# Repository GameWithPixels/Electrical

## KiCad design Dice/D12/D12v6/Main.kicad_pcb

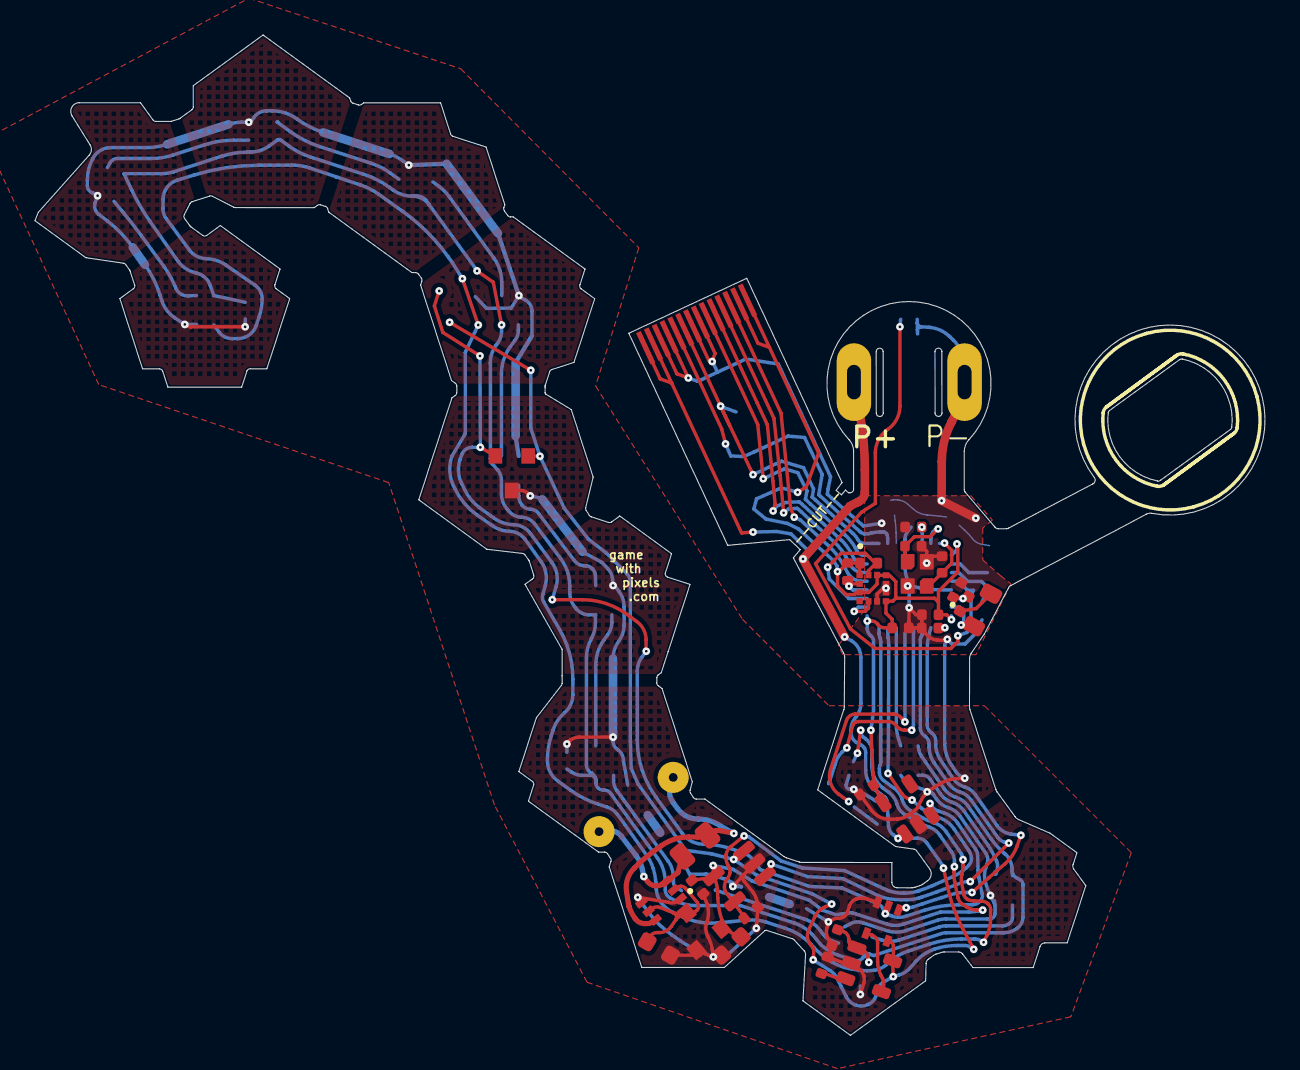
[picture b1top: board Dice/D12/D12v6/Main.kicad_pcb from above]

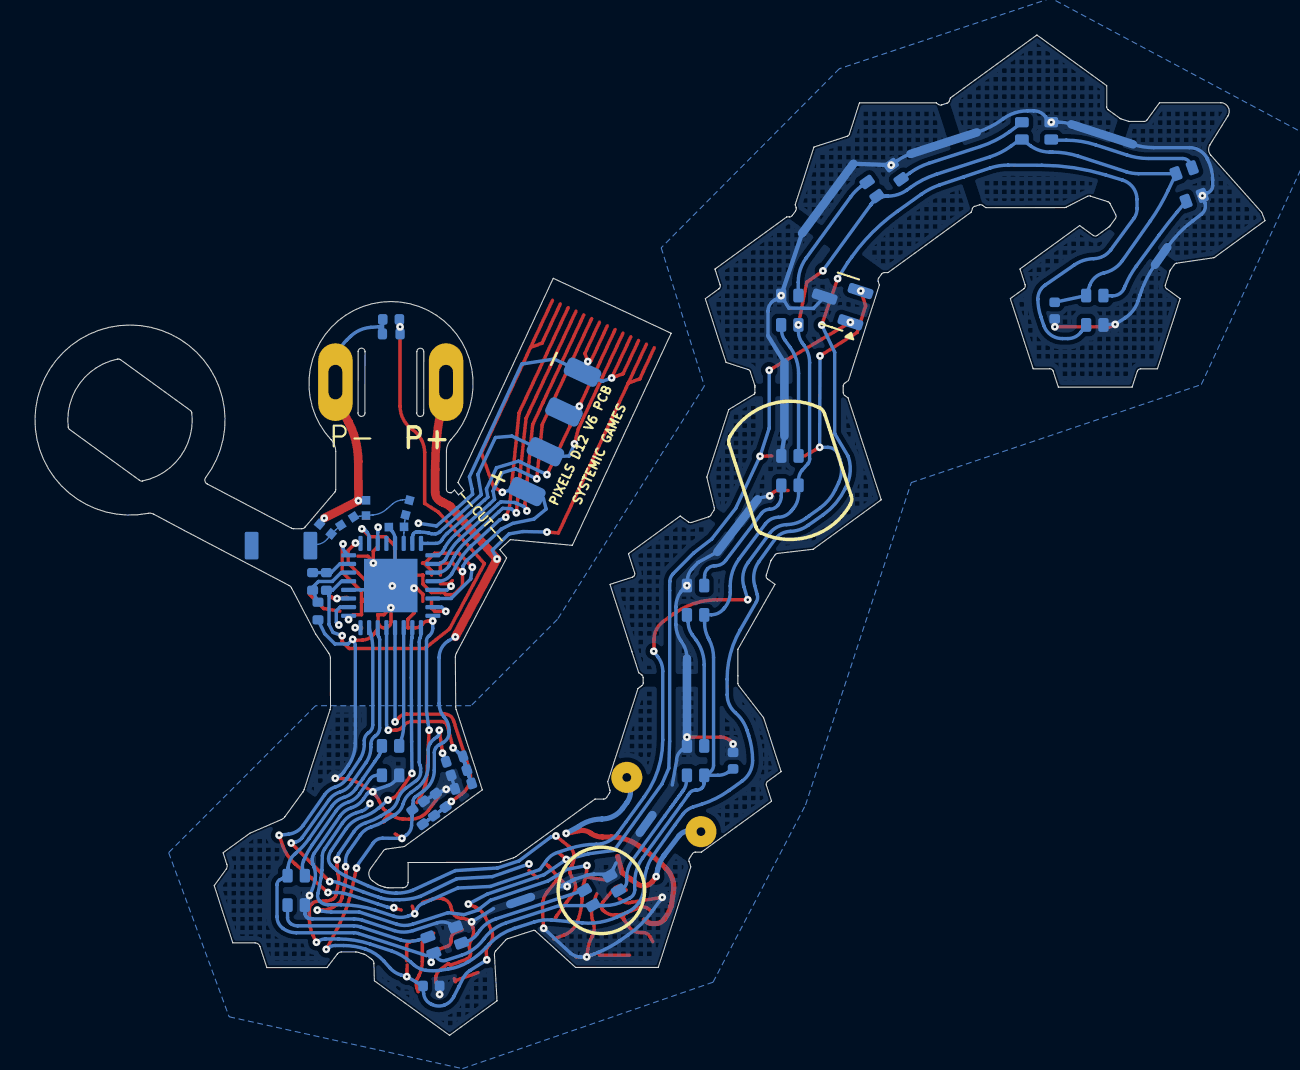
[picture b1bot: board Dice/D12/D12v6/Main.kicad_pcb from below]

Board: 2 copper layers, 71.2 x 57.9 mm, 67 parts (38 on the bottom side), 51 nets.

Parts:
AE1: Antenna_Chip; CHIP_ANT
C1, C4, C18: 4.7uF 10V 20%; C_0402_1005Metric
C2, C5: 8pF 10V 10%; C_0402_1005Metric
C3, C10, C23, C24: 0.1uF 10V 20%; C_0402_1005Metric
C6: DNP; C_0402_1005Metric
C7: 100pF NP0 10V 5%; C_0402_1005Metric
C8: 0.8pF 10V 5% C0G; 0402_RF
C9, C16: 10uF 10V 20%; C_0402_1005Metric
C11, C12: DNP; 0402_RF
C13: 4.7uF 25V 20%; C_0603_1608Metric
C15: 22uF 10V 20%; C_0603_1608Metric
C19: 12nF 50V 5% NP0; C_0805_2012Metric
C21, C22: 10nF 25V 10%; C_0402_1005Metric
D1: BAV99S; SOT-363_SC-70-6
D2, D3, D4, D5, D6, D7, D8, D9, D10, D11, D12, D13: TX1812Z_2020
J1: Conn_01x14; FPC_14
J2: Conn_01x04; FPC-POGO-4
J3: Conn_01x02; Hongjie 10100 Connector
L1: 10uH 100mA 20%; L_0805_2012Metric
L2: 15nH 100mA 5%; L_0402_1005Metric
L3: 0 Ohm; 0402_RF
L5: 3.9nH 5%; 0402_RF
P5: COILA; TestPoint_THTPad_D1.5mm_Drill0.7mm_nosilk
P6: COILB; TestPoint_THTPad_D1.5mm_Drill0.7mm_nosilk
R1, R2, R7: 4.02M 1%; R_0402_1005Metric
R3: 10k 5%; R_0402_1005Metric
R4, R6: 18k 1%; R_0402_1005Metric
R5, R10: 100k 1%; R_0402_1005Metric
R8: 10M 1%; R_0402_1005Metric
R9: 180k 1%; R_0402_1005Metric
R12, R16: 2.7k 5%; R_0402_1005Metric
TH1: NTC 100k @ 25C; R_0402_1005Metric
U1: N52810_QFN32; QFN-32-1EP_5x5mm_P0.5mm_EP3.1x3.1mm
U2: KXTJ3-1057; LGA-12_2x2mm_P0.5mm
U3: PJ75BL50SA; SOT-23
U4: ME6215; SOT-23-5
U5: MCP73832T-2ACI/OT; SOT-23-5
U6: MT9700; SOT-23-5
U7: SN74LVC1G08; SOT-353_SC-70-5
U8, U8-alt1: VCS2373S; SOT-23
Y1: 32MHz 40ppm; Crystal_SMD_2016-4Pin_2.0x1.6mm

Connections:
+5V: C15.1, R1.1, R4.1, U3.2 (VOUT), U5.4 (VDD)
+BATT: C16.1, J1.1, J1.2, J3.1, R7.1, U4.1 (VIN), U5.3 (VBAT), U6.5 (VIN), U7.5 (VCC), U8.1 (VCC), U8-alt1.1 (VCC)
/5V_SENSE: C21.1, R1.2, R2.2, U1.4 (P0.04/AIN2)
/ACC_INT: U1.10 (P0.12), U2.5 (INT)
/ANTENNA: AE1.1 (FEED), C11.1, L3.2
/ANT_50: C12.1, L3.1, L5.2
/ANT_NRF: C8.1, L5.1, U1.19 (ANT)
/BATT_NTC: C6.1, R5.2, TH1.1, U1.28 (P0.30/AIN6)
/LED_DATA: D2.1 (DIN), U1.6 (P0.06)
/LED_EN: U1.2 (P0.00/XL1), U7.1
/LED_RETURN: D13.3 (DOUT), U1.8 (P0.10)
/NTC_ID_VDD: R5.1, R10.2, U1.26 (P0.25)
/PROG: R6.1, U1.7 (P0.09), U5.5 (PROG)
/Power Supply/LED_EN_OUT: U6.4 (EN), U7.4
/Power Supply/MAG1_: U4.3 (CE), U7.2, U8.2 (OUT), U8-alt1.2 (OUT)
/SCL: R12.2, U1.11 (P0.14), U2.12 (SCL)
/SDA: R16.2, U1.12 (P0.15), U2.2 (SDA)
/STATS: U1.3 (P0.01/XL2), U5.1 (STAT)
/VBAT_SENSE: C22.1, R7.2, R8.1, U1.5 (P0.05/AIN3)
GND: C1.2, C2.1, C3.2, C4.2, C5.1, C6.2, C7.2, C8.2, C9.2, C10.2, C11.2, C12.2, C13.2, C15.2, C16.2, C18.2, C21.2, C22.2, C23.2, C24.2, D1.1 (A1), D1.4 (A3), D2.4 (GND), D3.4 (GND), D4.4 (GND), D5.4 (GND), D6.4 (GND), D7.4 (GND), D8.4 (GND), D9.4 (GND), D10.4 (GND), D11.4 (GND), D12.4 (GND), D13.4 (GND), J1.3, J1.4, J1.7, J1.8, J2.4, J3.2, R2.1, R3.2, R4.2, R6.2, R8.2, R9.1, TH1.2, U1.20 (VSS), U1.29 (VSS), U1.33 (VSS), U2.6 (GND), U2.8 (GND), U2.9 (GND), U3.1 (VSS), U4.2 (VSS), U5.2 (VSS), U6.2 (GND), U7.3 (GND), U8.3 (GND), U8-alt1.3 (GND), Y1.2, Y1.4
unnamed: C19.2, D1.6 (K3A4), P6.1
unnamed: C19.1, D1.3 (K1A2), P5.1
unnamed: D2.3 (DOUT), D3.1 (DIN)
unnamed: D3.3 (DOUT), D4.1 (DIN)
unnamed: D4.3 (DOUT), D5.1 (DIN)
unnamed: D5.3 (DOUT), D6.1 (DIN)
unnamed: D6.3 (DOUT), D7.1 (DIN)
unnamed: D7.3 (DOUT), D8.1 (DIN)
unnamed: D8.3 (DOUT), D9.1 (DIN)
unnamed: D9.3 (DOUT), D10.1 (DIN)
unnamed: D10.3 (DOUT), D11.1 (DIN)
unnamed: D11.3 (DOUT), D12.1 (DIN)
unnamed: D12.3 (DOUT), D13.1 (DIN)
unnamed: L1.2, L2.1
unnamed: L1.1, U1.31 (DCC)
unnamed: C3.1, U1.1 (DEC1)
unnamed: C7.1, U1.22 (DEC3)
unnamed: C1.1, L2.2, U1.30 (DEC4)
unnamed: R9.2, R10.1, U1.27 (P0.28/AIN4)
unnamed: C5.2, U1.23 (XC1), Y1.3
unnamed: C2.2, U1.24 (XC2), Y1.1
unnamed: R3.1, U6.3 (SET)
RESET: J1.9, U1.16 (P0.16)
RXI: J1.10, U1.15 (P0.20/TCLK)
SWDCLK: J1.6, J2.3, U1.17 (SWDCLK)
SWDIO: J1.5, J2.2, U1.18 (SWDIO)
SWO: J1.11, U1.14 (P0.18/TDATA0)
TXO: J1.12, U1.13 (P0.16/TDATA1)
VDC: C9.1, C23.1, C24.1, D2.2 (VCC), D3.2 (VCC), D4.2 (VCC), D5.2 (VCC), D6.2 (VCC), D7.2 (VCC), D8.2 (VCC), D9.2 (VCC), D10.2 (VCC), D11.2 (VCC), D12.2 (VCC), D13.2 (VCC), U6.1 (VOUT)
VDD: C4.1, C10.1, C18.1, J1.13, J1.14, J2.1, R12.1, R16.1, U1.9 (VDD), U1.25 (VDD), U1.32 (VDD), U2.1 (ADDR), U2.3 (IO_VDD), U2.7 (VDD), U2.10 (VDD), U2.11 (IO_VDD), U4.5 (VOUT)
VEE: C13.1, D1.2 (K2), D1.5 (K4), U3.3 (VIN)

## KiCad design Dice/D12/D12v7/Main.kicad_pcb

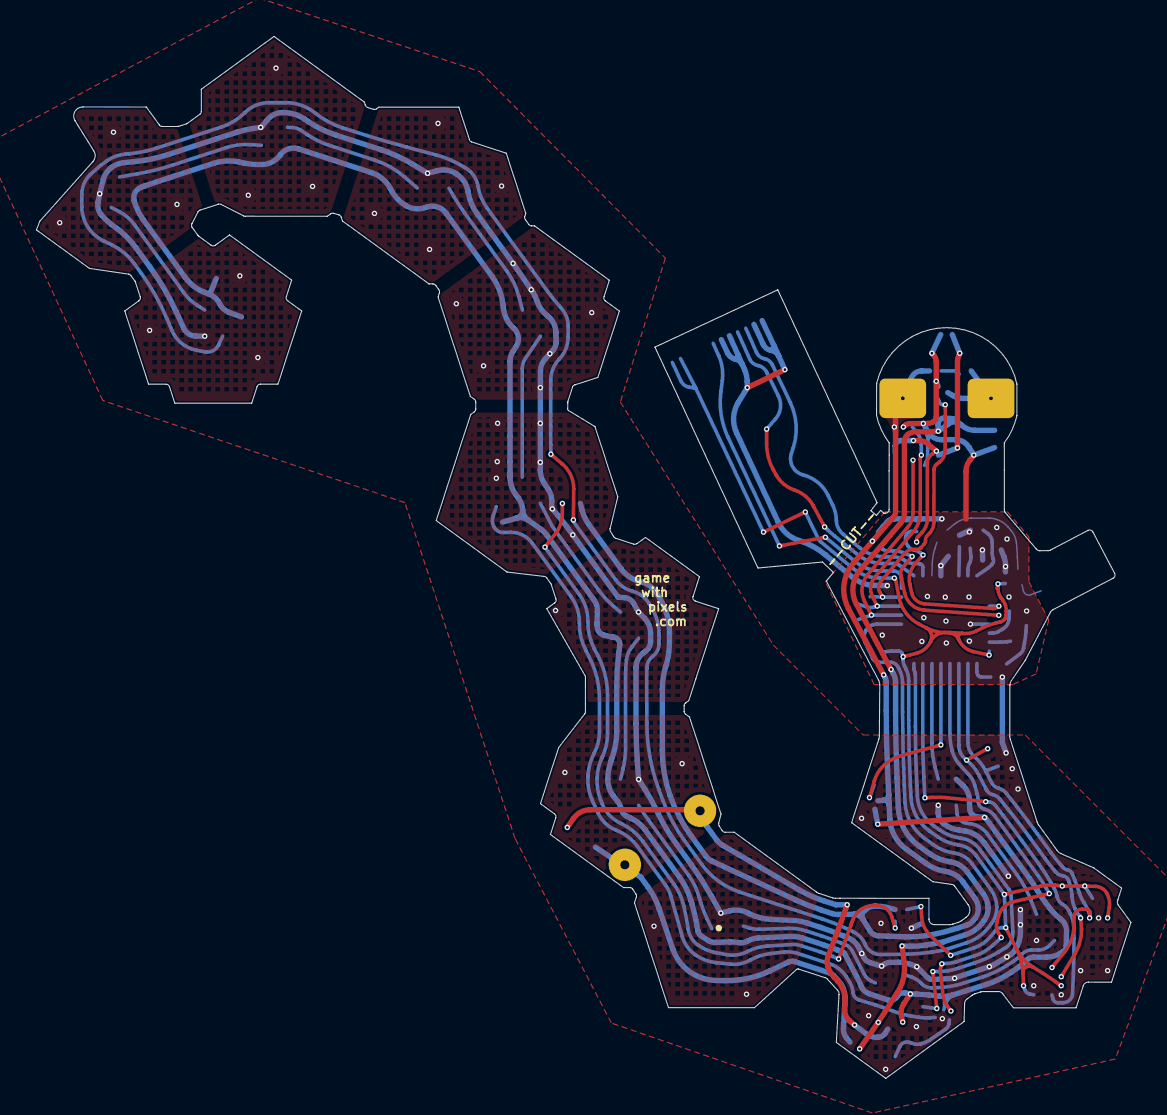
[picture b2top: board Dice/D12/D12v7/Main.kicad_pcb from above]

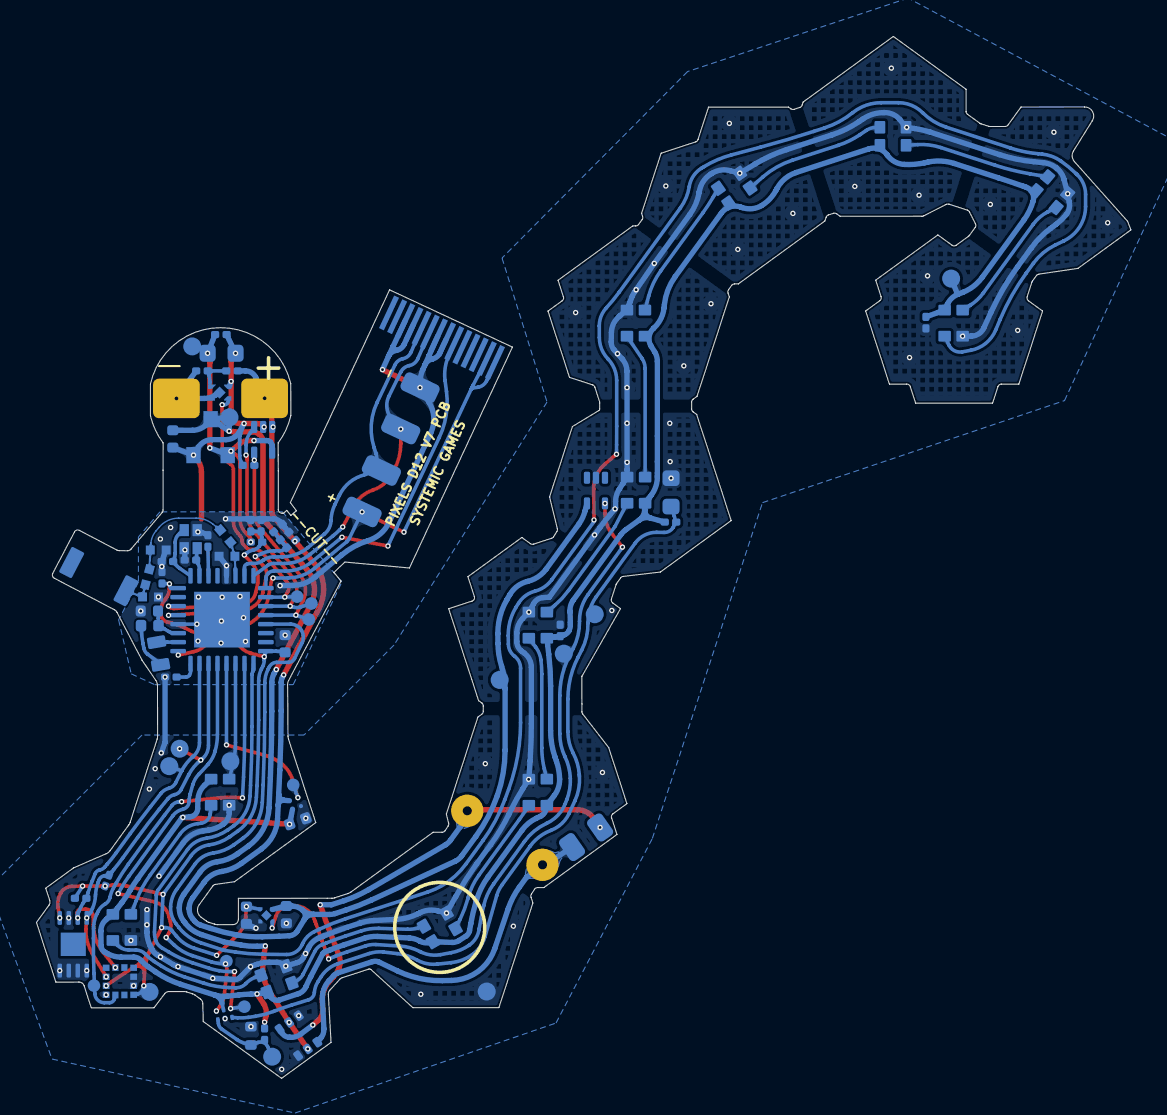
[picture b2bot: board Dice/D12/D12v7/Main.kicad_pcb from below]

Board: 2 copper layers, 60.8 x 57.9 mm, 87 parts (87 on the bottom side), 50 nets.

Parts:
AE1: Antenna_Chip; CHIP_ANT
C1, C4, C18: 4.7uF 10V 20%; C_0402_1005Metric
C2, C5: 8pF 10V 10%; C_0201_0603Metric
C3, C6, C10, C23, C24: 0.1uF 10V 20%; C_0201_0603Metric
C7: 100pF NP0 10V 2%; C_0201_0603Metric
C8: 0.8pF 10V 5% C0G; 0402_RF
C9, C16: 10uF 6.3V 20%; C_0402_1005Metric
C11, C12: DNP; 0402_RF
C13: 4.7uF 25V 20%; C_0402_1005Metric
C15: 22uF 10V 20%; C_0603_1608Metric
C19: 12nF 50V 5% NP0; C_0805_2012Metric
C21, C22: 10nF 25V 10%; C_0201_0603Metric
D1: BAV99S; SOT-363_SC-70-6
D2, D3, D4, D5, D6, D7, D8, D9, D10, D11, D12, D13: TX1812MWCA5-F01
J1: Conn_01x14; FPC_14
J2: Conn_01x04; FPC-POGO-4
J3: Conn_01x02; Hongjie 10100 Solder Tabs
L1: 10uH 100mA 20%; C_1.2x1.8
L2: 15nH 100mA 5%; L_0402_1005Metric
L3: 0 Ohm; 0402_RF
L5: 3.9nH 5%; 0402_RF
P5: COILA; TestPoint_THTPad_D1.5mm_Drill0.7mm_nosilk
P6: COILB; TestPoint_THTPad_D1.5mm_Drill0.7mm_nosilk
Q1: ZSPT-Z1608C-06F-Z4; D_0603_1608Metric
R1, R2, R7: 3.9M 1%; R_0201_0603Metric
R4, R5: 10k 1%; R_0201_0603Metric
R6, R10, R11: 3.9k 1%; R_0201_0603Metric
R8: 10M 1%; R_0201_0603Metric
R9: 100k 1%; R_0201_0603Metric
R12: 510R 1%; R_0201_0603Metric
TH1: NTC 100k @ 25C; R_0402_1005Metric
U1: N52810_QFN32; QFN-32-1EP_5x5mm_P0.5mm_EP3.1x3.1mm
U2: SC7A20HTR; LGA-12_2x2mm_P0.5mm
U3: PJ75BL50SA; SOT-23
U4: ME6230; FPB1_1-4
U5: BL24C02F-NTRC; TDFN-8-1EP_3x2mm_P0.5mm_EP1.3x1.4mm
U6: AW35122
U7: DS6101; UDFN-4-1EP_1x1mm_P0.65mm_EP0.48x0.48mm
U8: SL1605; SOT-553
U9: XT4051; SOT-553
U10: WAS3157D-6/TR; DFN1109-6
W1: LED_DATA1; TEST_PIN
W2: PROG; TEST_PIN
W3: PHOTO; TEST_PIN
W4: VDC; TEST_PIN
W5: SM; TEST_PIN
W6: MAG1; TEST_PIN
W7: ACC_INT; TEST_PIN
W8: SCL; TEST_PIN
W9: SDA; TEST_PIN
W14: BATT; TEST_PIN
W15: +5V; TEST_PIN
W16: VIN; TEST_PIN
W17: STAT; TEST_PIN
W19: GND; TEST_PIN
W20: TH1; TEST_PIN
W21: LED2; TEST_PIN
W22: ADC_SELECT; TEST_PIN
W23: ADC_OUT; TEST_PIN
W25: VDD; TEST_PIN
Y1: 32MHz 40ppm; SX16Y032000B81T001

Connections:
+5V: C15.1, R1.1, R4.1, U3.2 (VOUT), U9.5 (VCC), W15.1
+BATT: C16.1, J3.1, R7.1, R12.1, U4.4 (VIN), U6.A2 (VIN), U8.4 (VDD), U9.1 (BAT), W14.1
/5V_SENSE: C21.1, R1.2, R2.2, U1.27 (P0.28/AIN4)
/ACC_INT: U1.7 (P0.09), U2.5 (INT1), W7.1
/ANTENNA: AE1.1 (FEED), C11.1, L3.2
/ANT_50: C12.1, L3.1, L5.2
/ANT_NRF: C8.1, L5.1, U1.19 (ANT)
/LED_DATA: D2.3 (DIN), U1.6 (P0.06), W1.1
/LED_EN: U1.5 (P0.05/AIN3), U6.B2 (EN), W21.1
/LED_RETURN: D13.1 (DOUT), U1.12 (P0.15)
/MAG1_: U4.3 (CE), U8.5 (OUT), W6.1
/NTC_PHOTO_SENSE: U1.4 (P0.04/AIN2), U10.6 (A), W23.1
/OPT_A2D: Q1.1 (C), R5.2, U10.3 (B1), W3.1
/PROG: R6.1, U1.13 (P0.16/TDATA1), U9.4 (PROG), W2.1
/SCL: R10.2, U1.2 (P0.00/XL1), U2.12 (SCL), U5.6 (SCL), W8.1
/SDA: R11.2, U1.3 (P0.01/XL2), U2.2 (SDA), U5.5 (SDA), W9.1
/SENSE_SELECT: U1.8 (P0.10), U10.4 (S), W22.1
/SM: U1.15 (P0.20/TCLK), U7.3 (SM), W5.1
/STATS: U1.14 (P0.18/TDATA0), U9.3 (CHRG), W17.1
/VBAT_SENSE: C22.1, R7.2, R8.1, U1.28 (P0.30/AIN6)
/Wireless Charging/B-: C23.2, J3.2, U7.2 (VSS), U7.5 (PAD)
/Wireless Charging/COILA: C19.1, D1.3 (K1A2), P5.1
/Wireless Charging/COILB: C19.2, D1.6 (K3A4), P6.1
/Wireless Charging/TH1: R9.2, TH1.1, U10.1 (B0), W20.1
GND: C1.2, C2.1, C3.2, C4.2, C5.1, C6.2, C7.2, C8.2, C9.2, C10.2, C11.2, C12.2, C13.2, C15.2, C16.2, C18.2, C21.2, C22.2, C24.2, D1.1 (A1), D1.4 (A3), D2.2 (GND), D3.2 (GND), D4.2 (GND), D5.2 (GND), D6.2 (GND), D7.2 (GND), D8.2 (GND), D9.2 (GND), D10.2 (GND), D11.2 (GND), D12.2 (GND), D13.2 (GND), J1.3, J1.4, J1.7, J1.8, J2.4, Q1.2 (E), R2.1, R4.2, R6.2, R8.2, TH1.2, U1.20 (VSS), U1.29 (VSS), U1.33 (VSS), U2.4 (NC), U2.8 (GND), U2.9 (GND), U3.1 (VSS), U4.2 (VSS), U5.1 (A0), U5.2 (A1), U5.3 (A2), U5.4 (GND), U5.7 (WP), U6.B1 (GND), U7.4 (EB-), U8.2 (GND), U9.2 (GND), U10.2 (GND), W19.1, Y1.2, Y1.4
unnamed: D2.1 (DOUT), D3.3 (DIN)
unnamed: D3.1 (DOUT), D4.3 (DIN)
unnamed: D4.1 (DOUT), D5.3 (DIN)
unnamed: D5.1 (DOUT), D6.3 (DIN)
unnamed: D6.1 (DOUT), D7.3 (DIN)
unnamed: D7.1 (DOUT), D8.3 (DIN)
unnamed: D8.1 (DOUT), D9.3 (DIN)
unnamed: D9.1 (DOUT), D10.3 (DIN)
unnamed: D10.1 (DOUT), D11.3 (DIN)
unnamed: D11.1 (DOUT), D12.3 (DIN)
unnamed: D12.1 (DOUT), D13.3 (DIN)
unnamed: L1.2, L2.1
unnamed: L1.1, U1.31 (DCC)
unnamed: C3.1, U1.1 (DEC1)
unnamed: C7.1, U1.22 (DEC3)
unnamed: C1.1, L2.2, U1.30 (DEC4)
unnamed: C5.2, U1.23 (XC1), Y1.3
unnamed: C2.2, U1.24 (XC2), Y1.1
unnamed: C23.1, R12.2, U7.1 (BAT)
RESET: J1.9, U1.16 (P0.16)
SWDCLK: J1.6, J2.3, U1.17 (SWDCLK)
SWDIO: J1.5, J2.2, U1.18 (SWDIO)
VDC: C6.1, C9.1, C24.1, D2.4 (VCC), D3.4 (VCC), D4.4 (VCC), D5.4 (VCC), D6.4 (VCC), D7.4 (VCC), D8.4 (VCC), D9.4 (VCC), D10.4 (VCC), D11.4 (VCC), D12.4 (VCC), D13.4 (VCC), R5.1, R9.1, U6.A1 (VOUT), U10.5 (VCC), W4.1
VDD: C4.1, C10.1, C18.1, J1.13, J1.14, J2.1, R10.1, R11.1, U1.9 (VDD), U1.25 (VDD), U1.32 (VDD), U2.3 (IO_VDD), U2.7 (VDD), U4.1 (VOUT), U5.8 (VCC), W25.1
VEE: C13.1, D1.2 (K2), D1.5 (K4), U3.3 (VIN), W16.1

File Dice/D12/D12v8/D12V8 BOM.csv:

"Reference","Qty","Value","Footprint","Manufacturer","Part Number"
"AE1","1","Antenna_Chip","Pixels-dice:CHIP_ANT","Microgate","MGMA3216H2450-A02"
"C1,C4,C18","3","4.7uF 10V 20%","Pixels-dice:C_0402_1005Metric","HRE","CGA0402X5R475M100GT"
"C2,C5","2","8pF 10V 10%","Capacitor_SMD:C_0201_0603Metric","HRE","CGA0201C0G8R0B250ET"
"C3,C6,C10,C23,C24","5","0.1uF 10V 20%","Capacitor_SMD:C_0201_0603Metric","HRE","CGA0201X5R104K100ET"
"C7","1","100pF NP0 10V 2%","Capacitor_SMD:C_0201_0603Metric","HRE","CGA0201C0G101J500ET"
"C8","1","0.8pF 10V 5% C0G","Capacitor_SMD:C_0201_0603Metric","HRE","CGA0201C0GR80C250ET"
"C9,C16","2","10uF 6.3V 20%","Pixels-dice:C_0402_1005Metric","HRE","CGA0402X5R106M6R3GT"
"C13","1","4.7uF 25V 20%","Capacitor_SMD:C_0402_1005Metric","HRE","CGA0402X5R475M250GT"
"C15","1","22uF 10V 20%","Capacitor_SMD:C_0603_1608Metric","HRE","CGA0603X5R226M100JT"
"C19","1","12nF 50V 5% NP0","Capacitor_SMD:C_0805_2012Metric","Murata","GRM2195C1H123JA01D"
"C21,C22","2","10nF 25V 10%","Capacitor_SMD:C_0201_0603Metric","HRE","CGA0201X5R103K250ET"
"D1","1","BAV99S","Pixels-dice:SOT-363_SC-70-6","Nexperia","BAV99S,115"
"D2,D3,D4,D5,D6,D7,D8,D9,D10,D11,D12,D13","12","TX1812MWCA5-F01","Pixels-dice:TX1812MWCA5-F01","TCWIN","TX1812MWCA5-F01"
"L1","1","10uH 100mA 20%","Inductor_SMD:L_0603_1608Metric","FH","CMI160808J100KT"
"L2","1","15nH 100mA 5%","Inductor_SMD:L_0201_0603Metric","FH","VHF060303HQ15NKT"
"L3","1","0 Ohm","Resistor_SMD:R_0201_0603Metric","UNI-ROYAL(Uniroyal Elec)","0201WMF0000TEE"
"L5","1","3.9nH 5%","Inductor_SMD:L_0201_0603Metric","FH"," VHF060303HQ3N9ST02"
"R1,R2,R7","3","3.9M 1%","Resistor_SMD:R_0201_0603Metric","UNI-ROYAL(Uniroyal Elec)","0201WMF3904TEE"
"R3","1","681k 1%","Resistor_SMD:R_0201_0603Metric","UNI-ROYAL(Uniroyal Elec)","0201WMF6813TEE"
"R4","1","10k 1%","Resistor_SMD:R_0201_0603Metric","UNI-ROYAL(Uniroyal Elec)","0201WMF1002TEE"
"R5,R9","2","100k 1%","Resistor_SMD:R_0201_0603Metric","UNI-ROYAL(Uniroyal Elec)","0201WMF1003TEE"
"R6","1","3.57k 1%","Resistor_SMD:R_0201_0603Metric","UNI-ROYAL(Uniroyal Elec)","0201WMF3571TEE"
"R8","1","10M 1%","Resistor_SMD:R_0201_0603Metric","UNI-ROYAL(Uniroyal Elec)","0201WMF1005TEE"
"R10,R11","2","3.9k 1%","Resistor_SMD:R_0201_0603Metric","UNI-ROYAL(Uniroyal Elec)","0201WMF3651TEE"
"R12","1","510R 1%","Resistor_SMD:R_0201_0603Metric","UNI-ROYAL(Uniroyal Elec)","NQ01WMJ0511TEE"
"TH1","1","NTC 100k @ 25C","Resistor_SMD:R_0201_0603Metric","muRata ","NCP03WF104F05RL "
"U1","1","N52810_QFN32","Pixels-dice:QFN-32-1EP_5x5mm_P0.5mm_EP3.1x3.1mm","Nordic Semiconductor","NRF52810-QCAA-R"
"U2","1","SC7A20HTR","Package_LGA:LGA-12_2x2mm_P0.5mm","Hangzhou Silan Microelectronics","SC7A20HTR"
"U3","1","PJ75BL50SA","Pixels-dice:SOT-23","PJSEMI","PJ75BL50SA"
"U4","1","ME6230","Pixels-dice:FPB1_1-4","MICRONE(Nanjing Micro One Elec)","ME6230C30U4AG"
"U5","1","BL24C02F-NTRC","Pixels-dice:TDFN-8-1EP_3x2mm_P0.5mm_EP1.3x1.4mm","BL","BL24C02F-NTRC"
"U6","1","AW35122","Pixels-dice:AW35122","AWINIC(Shanghai Awinic Tech)","AW35122FDR"
"U7","1","DS6101","Package_DFN_QFN:UDFN-4-1EP_1x1mm_P0.65mm_EP0.48x0.48mm","DSTECH"," DS6101AED4"
"U8","1","SL1605","Package_TO_SOT_SMD:SOT-553","Slkor(SLKORMICRO Elec.)","SL1605TL"
"U9","1","XT4051","Package_TO_SOT_SMD:SOT-553","NATLINEAR","XT4051K421KR-G"
"Y1","1","32MHz 40ppm","Pixels-dice:Crystal_SMD_2016-4Pin_2.0x1.6mm","TOGNJING","XTM20032000DT00351001"

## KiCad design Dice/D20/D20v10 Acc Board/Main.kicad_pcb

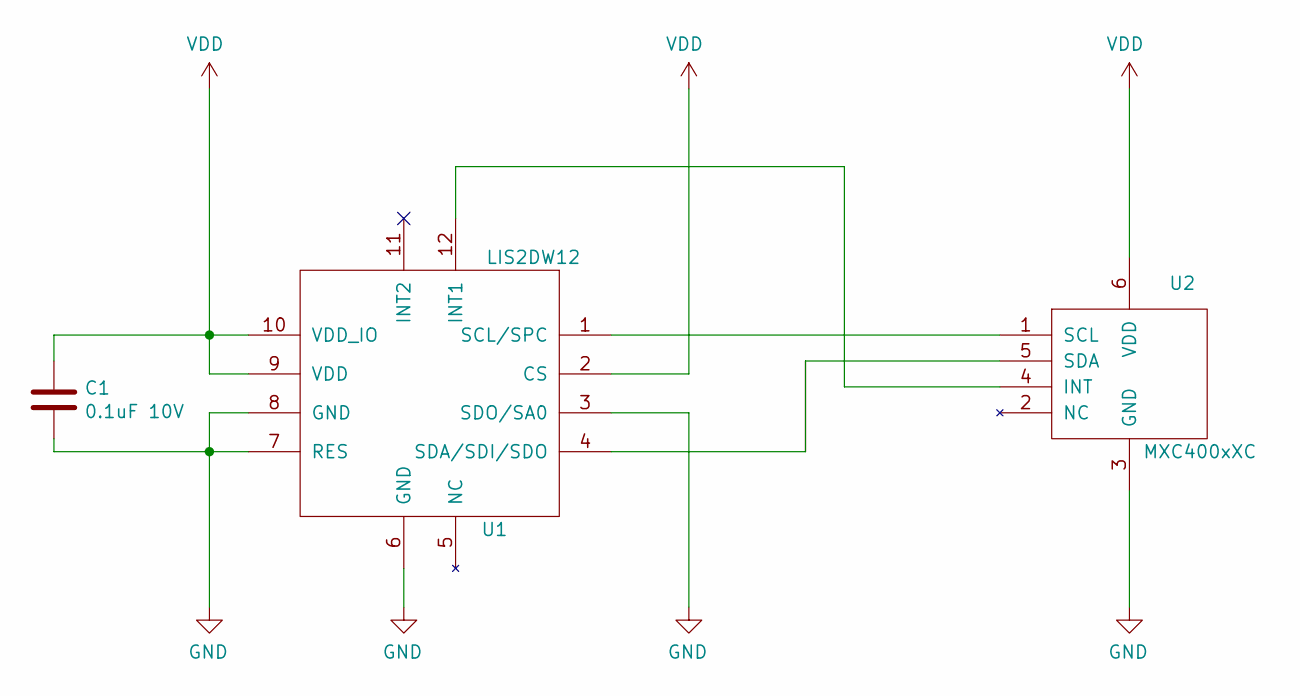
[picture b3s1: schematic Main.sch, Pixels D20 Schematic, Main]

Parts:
C1: 0.1uF 10V; C_0402_1005Metric
U1: LIS2DW12; LGA-12_2x2mm_Pitch0.5mm
U2: MXC400xXC; WLP-6-Flipped; Manufacturer Part Number MXC4005XC

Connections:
GND: C1.2, U1.3 (SDO/SA0), U1.6 (GND), U1.7 (RES), U1.8 (GND), U2.3 (GND)
unnamed: U1.1 (SCL/SPC), U2.1 (SCL)
unnamed: U1.4 (SDA/SDI/SDO), U2.5 (SDA)
unnamed: U1.12 (INT1), U2.4 (INT)
VDD: C1.1, U1.2 (CS), U1.9 (VDD), U1.10 (VDD_IO), U2.6 (VDD)

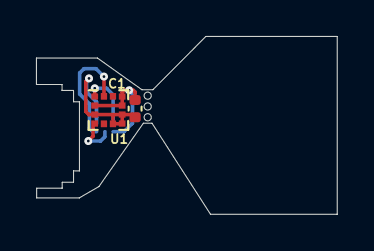
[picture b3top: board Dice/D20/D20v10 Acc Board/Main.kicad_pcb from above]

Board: 2 copper layers, 16.7 x 9.9 mm, 3 parts (1 on the bottom side), 5 nets.
